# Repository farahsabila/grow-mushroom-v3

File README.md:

# IoT-based Mushroom Cultivation Device v3
This was my Exhibition Project that I showcased at INAGRITECH 2023 on August 23 - 25, 2023. This prototype was made for growing any mushroom at home. 

## How It Works
Air humidity, air temperature, and light intensity are being monitored and controlled using IoT Technology. 

With these parameter specifications:
1. Air humidity: 70 % - 95 %
2. Air temperature: 20 °C - 25 °C
3. Light intensity: 300 lx - 500 lx

This range parameter specification can be adjusted according to the type of mushroom being chosen.

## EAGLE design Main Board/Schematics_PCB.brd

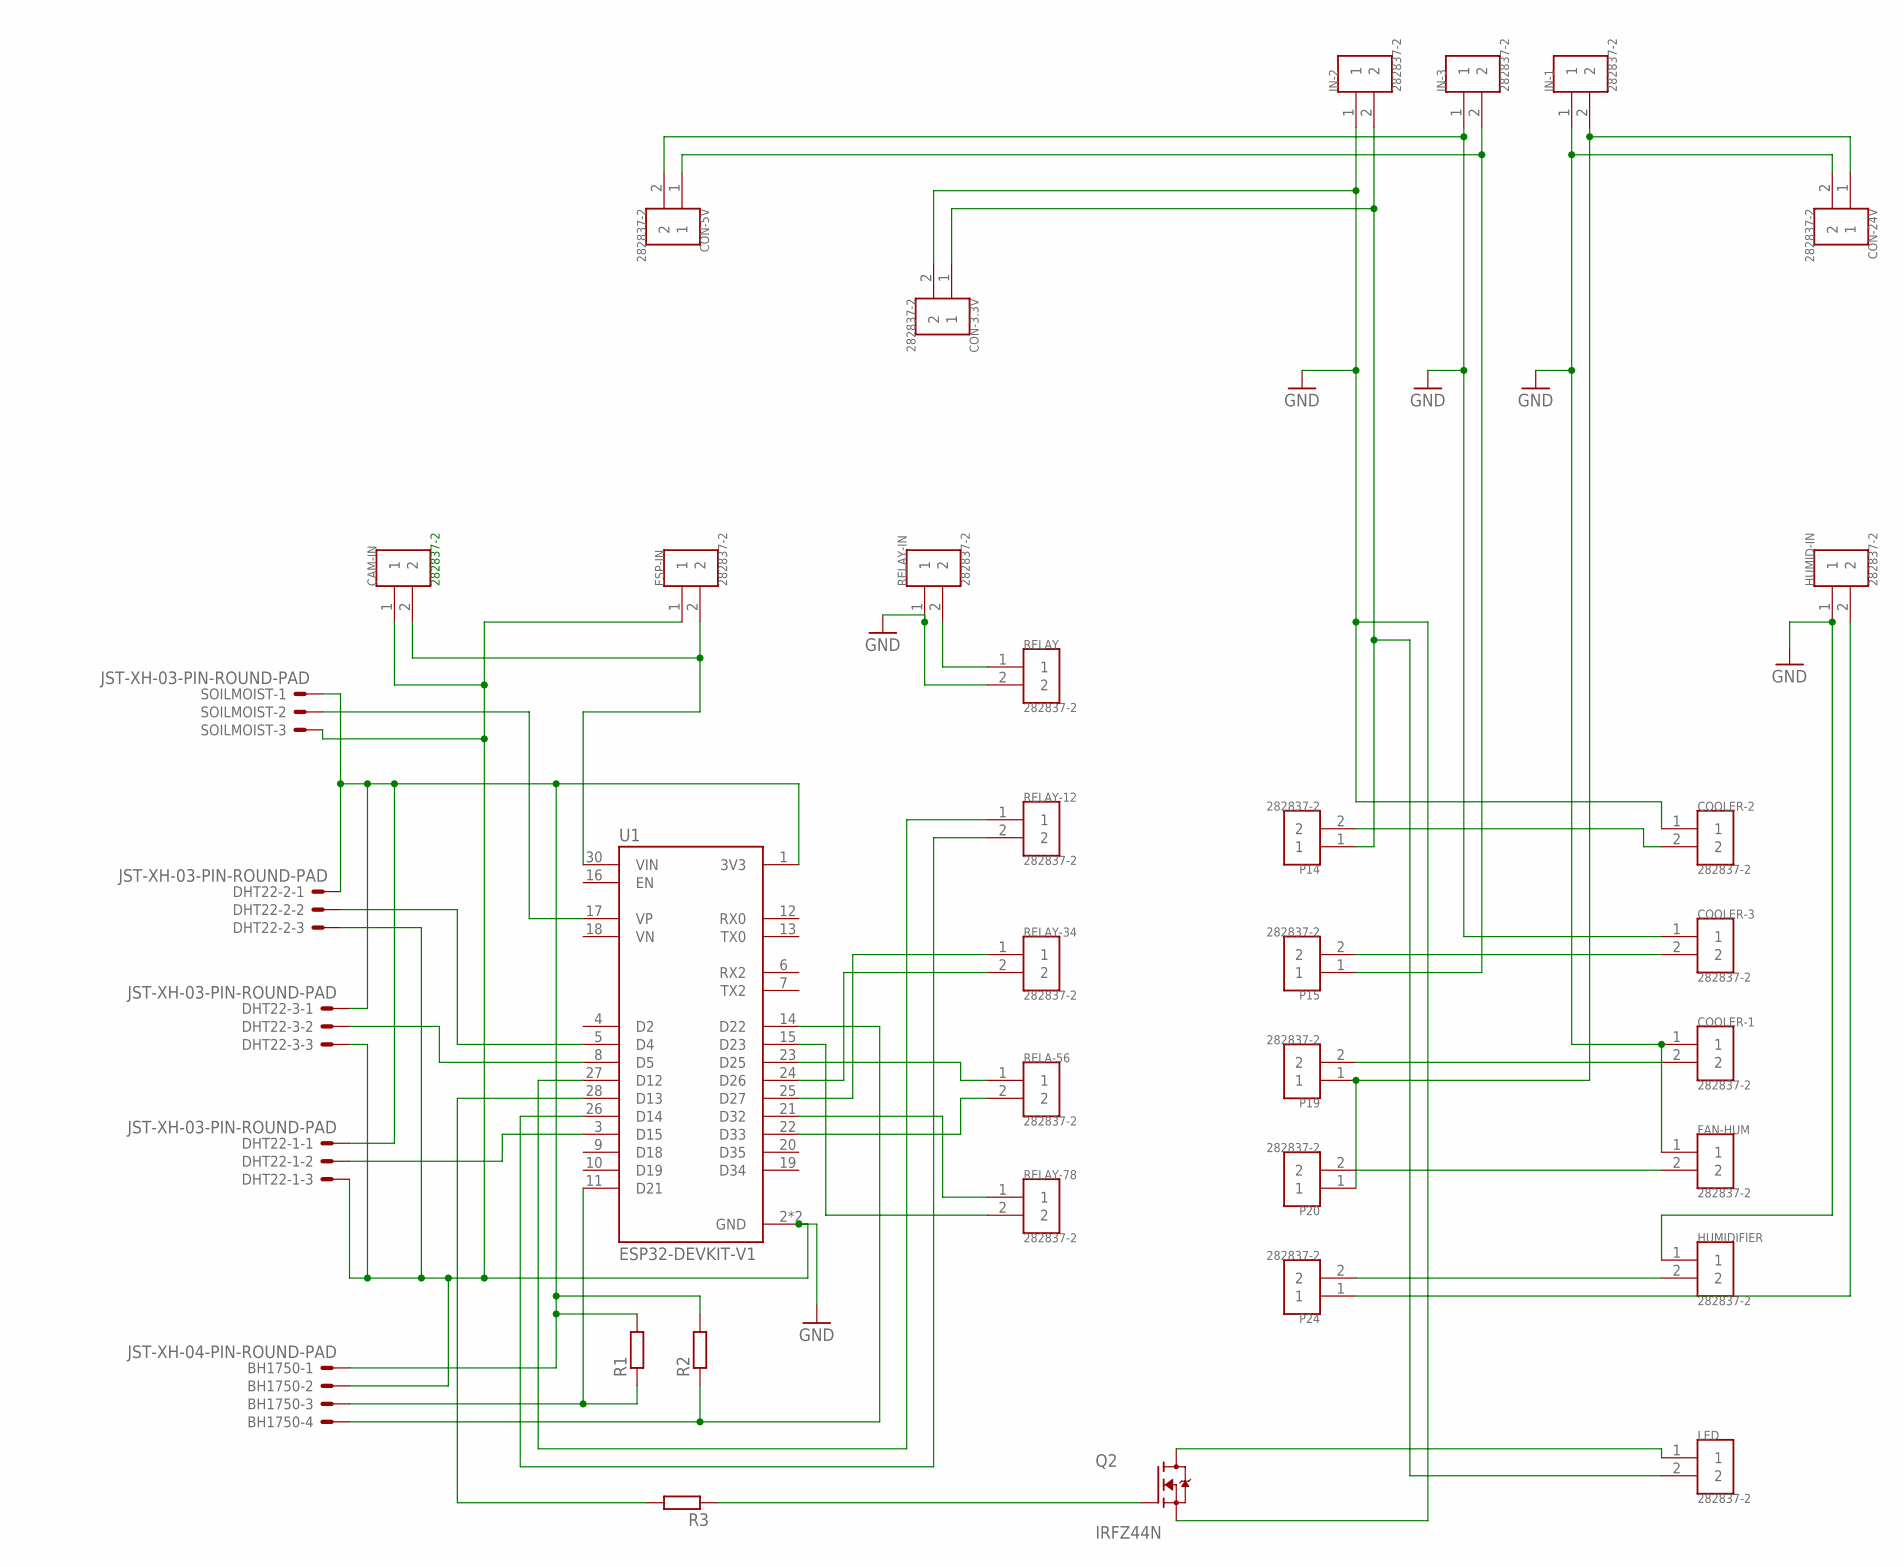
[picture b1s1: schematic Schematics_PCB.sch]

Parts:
BH1750: JST-XH-04-PIN-ROUND-PAD; JST-XH-04-PACKAGE-ROUND-PAD
CAM-IN: 282837-2; TE_282837-2
CON-3.3V, CON-5V, CON-24V: 282837-2; TE_282837-2
COOLER-1, COOLER-2, COOLER-3: 282837-2; TE_282837-2
DHT22-1, DHT22-2, DHT22-3: JST-XH-03-PIN-ROUND-PAD; JST-XH-03-PACKAGE-ROUND-PAD
ESP-IN: 282837-2; TE_282837-2
FAN-HUM: 282837-2; TE_282837-2
HUMID-IN: 282837-2; TE_282837-2
HUMIDIFIER: 282837-2; TE_282837-2
IN-1, IN-2, IN-3: 282837-2; TE_282837-2
LED: 282837-2; TE_282837-2
P14, P15, P19, P20, P24: 282837-2; TE_282837-2
Q2: IRFZ44N; TO254P1016X419X2286-3
R1, R2, R3: R-EU_0207/10; 0207/10
RELA-56: 282837-2; TE_282837-2
RELAY: 282837-2; TE_282837-2
RELAY-12, RELAY-34, RELAY-78: 282837-2; TE_282837-2
RELAY-IN: 282837-2; TE_282837-2
SOILMOIST: JST-XH-03-PIN-ROUND-PAD; JST-XH-03-PACKAGE-ROUND-PAD
U1: ESP32-DEVKIT-V1; MODULE_ESP32_DEVKIT_V1

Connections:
GND: BH1750.2, CAM-IN.1, CON-3.3V.2, CON-5V.2, CON-24V.2, COOLER-1.1, COOLER-2.1, COOLER-3.1, DHT22-1.3, DHT22-2.3, DHT22-3.3, ESP-IN.1, FAN-HUM.1, HUMID-IN.1, HUMIDIFIER.1, IN-1.1, IN-2.1, IN-3.1, Q2.3 (S), RELAY.2, RELAY-IN.1, SOILMOIST.3, U1.2 (GND), U1.29 (GND)
unnamed: DHT22-2.2, U1.5 (D4)
unnamed: DHT22-3.2, U1.8 (D5)
unnamed: SOILMOIST.2, U1.17 (VP)
unnamed: DHT22-1.2, U1.3 (D15)
unnamed: BH1750.1, DHT22-1.1, DHT22-2.1, DHT22-3.1, R1.2, R2.2, SOILMOIST.1, U1.1 (3V3)
unnamed: RELAY-12.1, U1.27 (D12)
unnamed: BH1750.3, R1.1, U1.11 (D21)
unnamed: BH1750.4, R2.1, U1.14 (D22)
unnamed: RELAY-12.2, U1.26 (D14)
unnamed: RELAY-34.1, U1.25 (D27)
unnamed: RELAY-34.2, U1.24 (D26)
unnamed: RELA-56.1, U1.23 (D25)
unnamed: RELA-56.2, U1.22 (D33)
unnamed: RELAY-78.1, U1.21 (D32)
unnamed: RELAY-78.2, U1.15 (D23)
unnamed: CAM-IN.2, ESP-IN.2, U1.30 (VIN)
unnamed: RELAY.1, RELAY-IN.2
unnamed: CON-3.3V.1, IN-2.2, LED.2, P14.1
unnamed: COOLER-2.2, P14.2
unnamed: CON-5V.1, IN-3.2, P15.1
unnamed: COOLER-3.2, P15.2
unnamed: CON-24V.1, IN-1.2, P19.1, P20.1
unnamed: COOLER-1.2, P19.2
unnamed: FAN-HUM.2, P20.2
unnamed: HUMIDIFIER.2, P24.2
unnamed: HUMID-IN.2, P24.1
unnamed: R3.2, U1.28 (D13)
unnamed: Q2.1 (G), R3.1
unnamed: LED.1, Q2.2 (D)

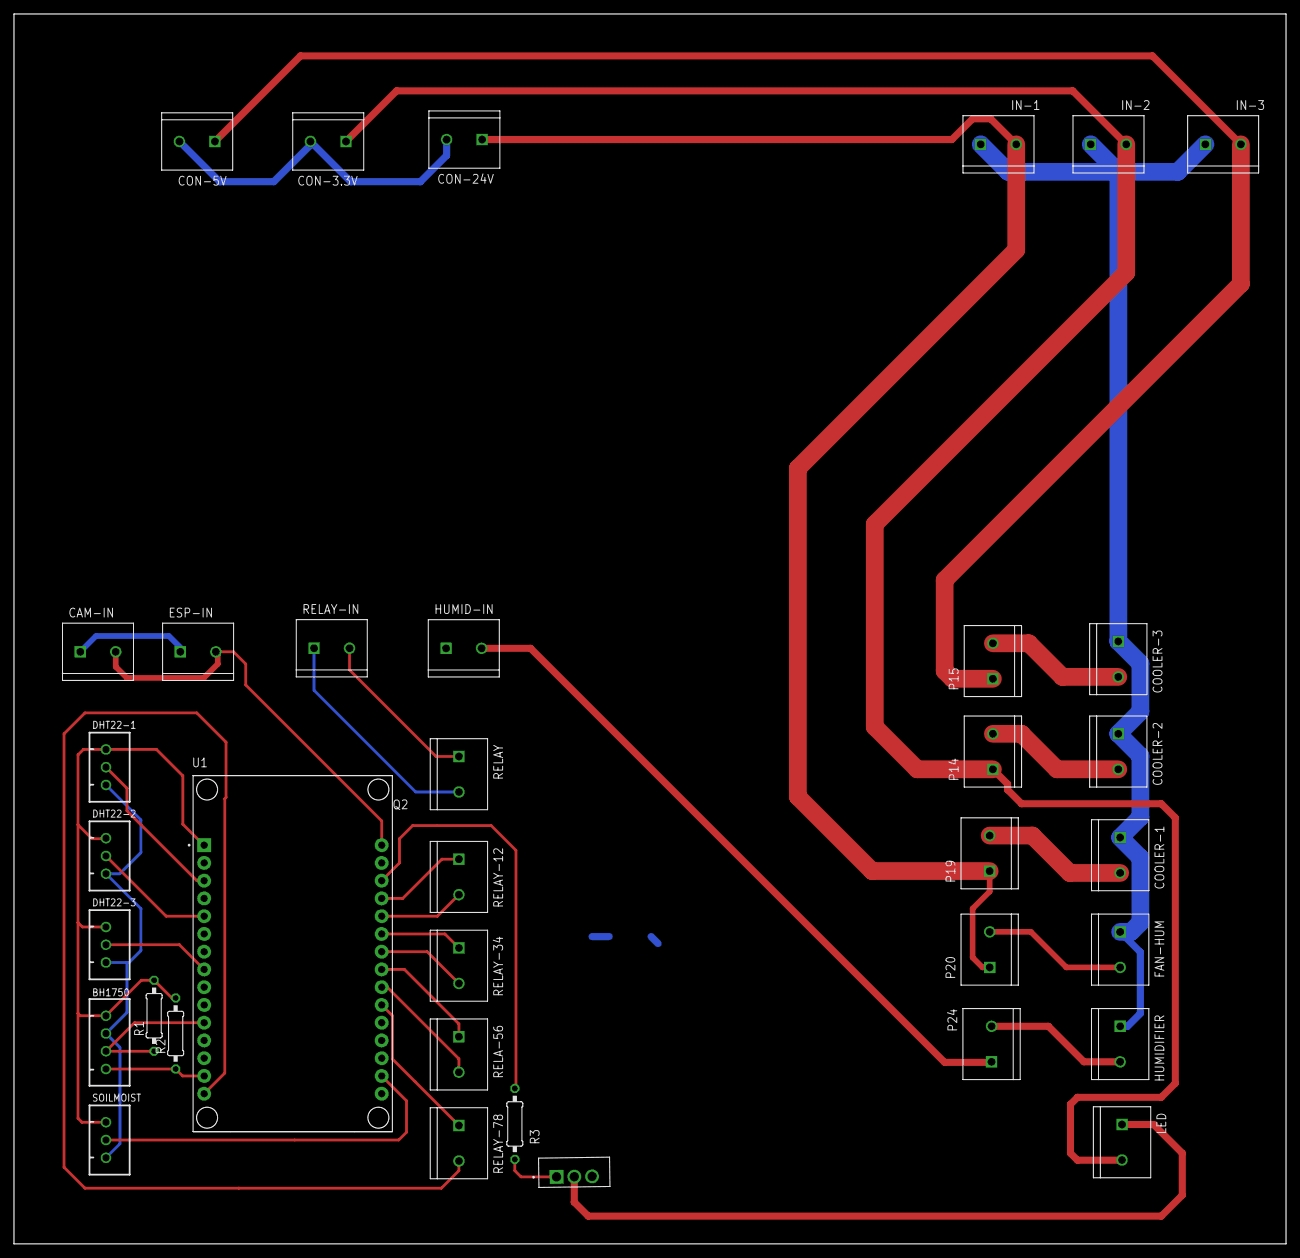
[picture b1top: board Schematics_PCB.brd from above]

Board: 2 copper layers, 182.0 x 176.0 mm, 36 parts (0 on the bottom side), 30 nets.

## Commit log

2023-12-28 add: main code
2023-12-28 add: casing
2023-12-28 add: camera code
2023-12-29 add: PCB design
2023-12-29 add: google script
